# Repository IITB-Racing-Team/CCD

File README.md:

# Overview
### Contains all the files related to Electrical System of IITB-Racing.

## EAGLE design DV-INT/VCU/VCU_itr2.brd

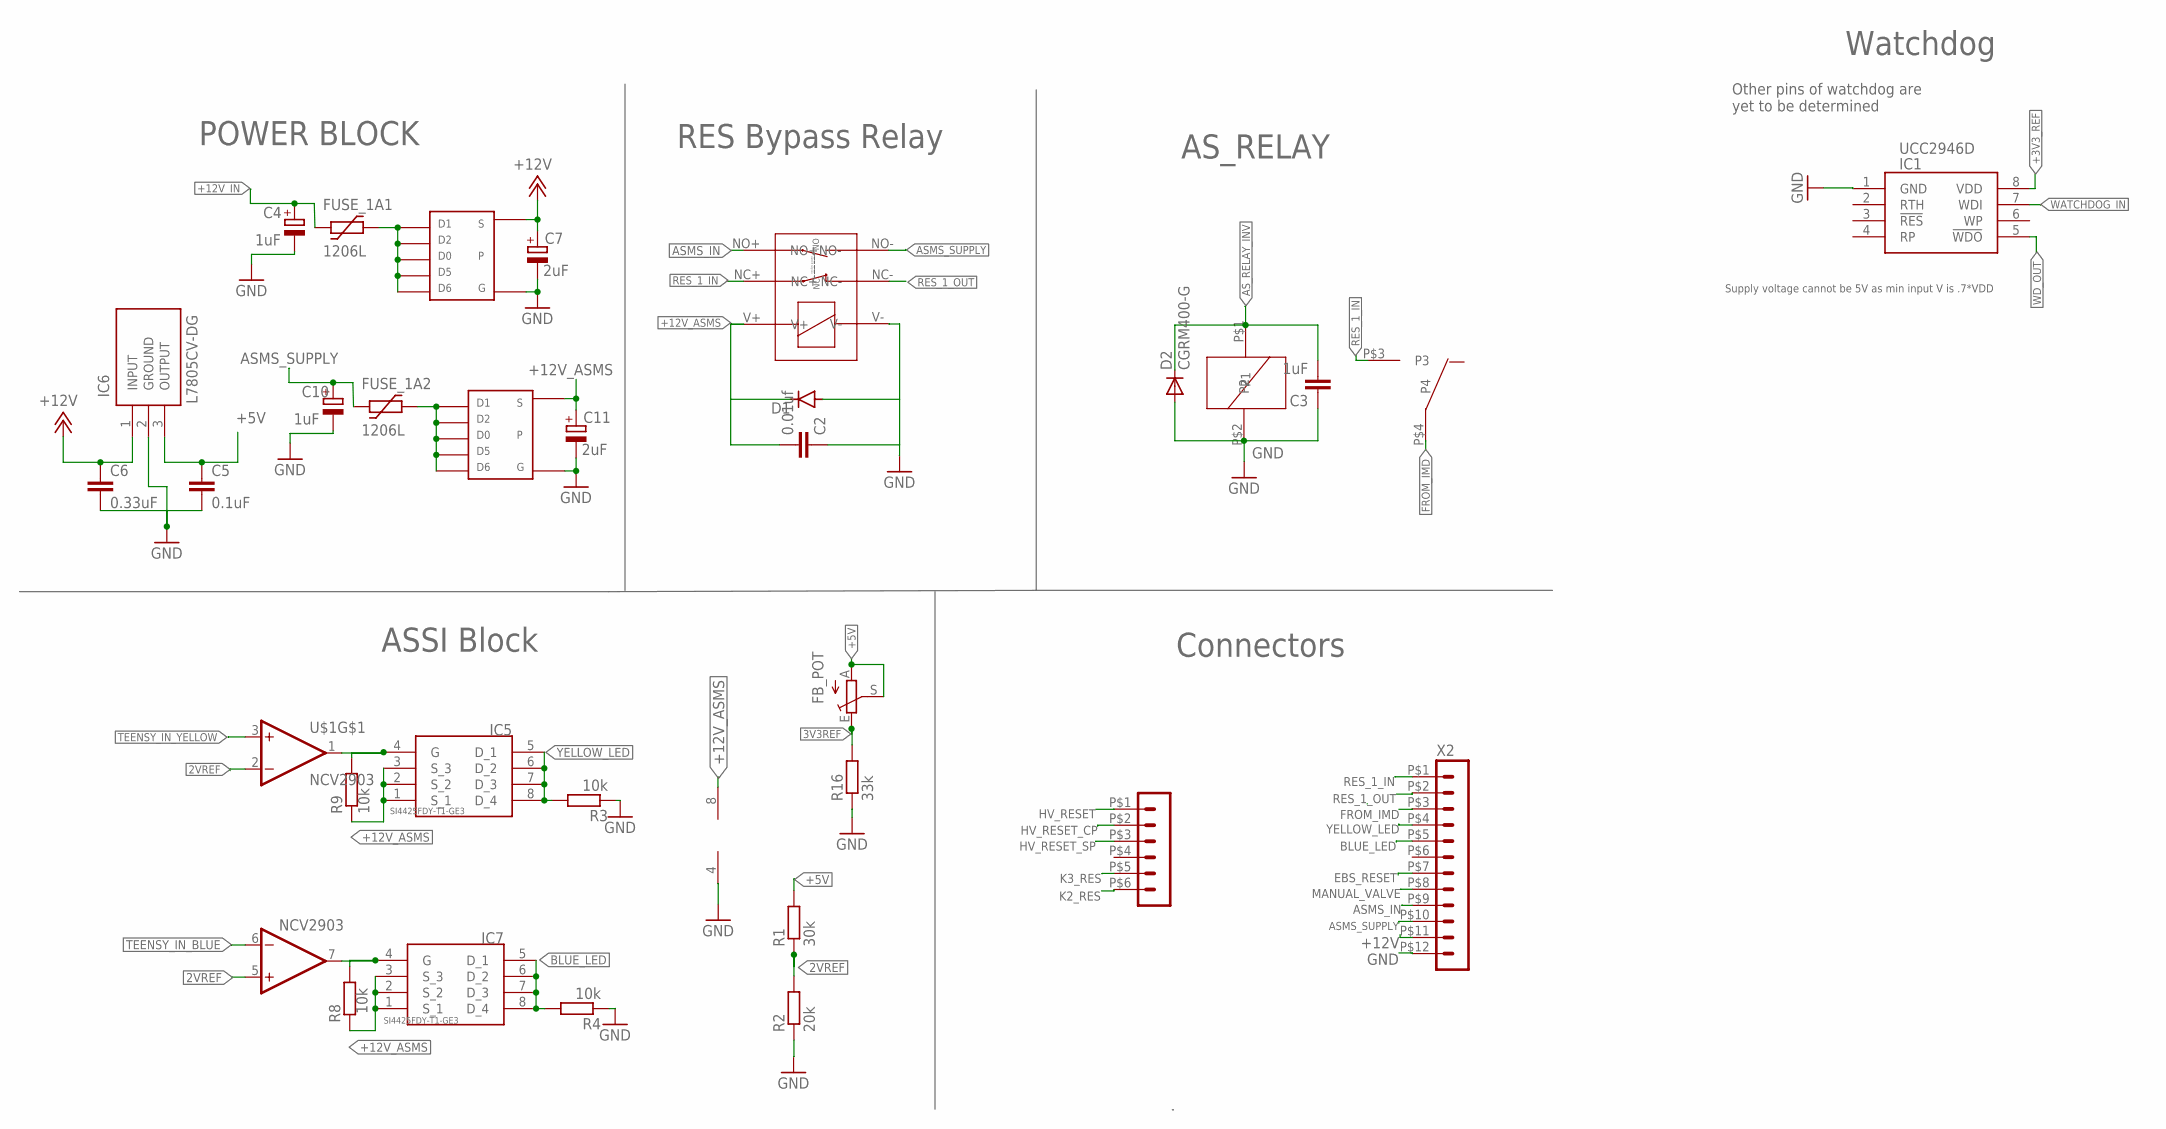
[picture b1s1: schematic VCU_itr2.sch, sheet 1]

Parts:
BMS-CONN7: HEADER_POS6_43045-0612; 43045-0612
C2: 0.01uf; C1210
C3: 1uF; C0805
C4, C10: 1uF; SMC_A
C5: 0.1uF; C0805
C6: 0.33uF; C0805
C7, C11: 2uF; E2,5-6
D1: DIODE-DO214AC; DO214AC
D2: CGRM400-G; SOD-123_MINI-SMA
FB_POT: 17k; S63S
FUSE_1A1, FUSE_1A2: 1206L
IC1: UCC2946D; SOIC127P600X175-8N
IC5, IC7: SI4425FDY-T1-GE3; SOIC127P600X175-8N
IC6: L7805CV-DG; TO255P460X1020X2008-3P
R1: 30k; M0805
R2: 20k; M0805
R3, R4, R8, R9: 10k; M0805
R16: 33k; M0805
SI1, SI4: TSOP-6_PMOS
U$1: NCV2903; SOIC-8
U$2: G6DN_RELAY
U$9: SFM_RELAY
X2: HEADER_POS12_44914-1201; 44914-1201

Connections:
2VREF: R1.1, R2.2, U$1.2 (-IN), U$1.5 (+IN); also elsewhere on the board
3V3REF: FB_POT.E, R16.2; also elsewhere on the board
+3V3_REF: IC1.8 (VDD)
+5V: C5.1, FB_POT.A, FB_POT.S, IC6.3 (OUTPUT), R1.2; also elsewhere on the board
+12V: C6.1, C7.+, IC6.1 (INPUT), SI1.S, X2.P$11 (11); also elsewhere on the board
+12V_ASMS: C2.2, C11.+, D1.C, IC5.1 (S_1), IC5.2 (S_2), IC5.3 (S_3), IC7.1 (S_1), IC7.2 (S_2), IC7.3 (S_3), R8.1, R9.1, SI4.S, U$1.8 (V+), U$9.V+; also elsewhere on the board
+12V_IN: C4.+, FUSE_1A1.P$1 (1)
ASMS_IN: U$9.NO+, X2.P$9 (9)
ASMS_SUPPLY: C10.+, FUSE_1A2.P$1 (1), U$9.NO-, X2.P$10 (10)
AS_RELAY_INV: C3.2, D2.C, U$2.P$1 (P1); also elsewhere on the board
BLUE_LED: IC7.5 (D_1), IC7.6 (D_2), IC7.7 (D_3), IC7.8 (D_4), R4.2, X2.P$5 (5)
EBS_RESET: X2.P$7 (7)
FROM_IMD: U$2.P$4 (P4), X2.P$3 (3)
GND: C2.1, C3.1, C4.-, C5.2, C6.2, C7.-, C10.-, C11.-, D1.A, D2.A, IC1.1 (GND), IC6.2 (GROUND), R2.1, R3.1, R4.1, R16.1, SI1.G, SI4.G, U$1.4 (V-), U$2.P$2 (P2), U$9.V-, X2.P$12 (12); also elsewhere on the board
HV_RESET: BMS-CONN7.P$1 (1); also elsewhere on the board
HV_RESET_CP: BMS-CONN7.P$2 (2); also elsewhere on the board
HV_RESET_SP: BMS-CONN7.P$3 (3); also elsewhere on the board
K2_RES: BMS-CONN7.P$6 (6)
K3_RES: BMS-CONN7.P$5 (5)
MANUAL_VALVE: X2.P$8 (8); also elsewhere on the board
unnamed: IC7.4 (G), R8.2, U$1.7 (OUT)
unnamed: IC5.4 (G), R9.2, U$1.1 (OUT)
unnamed: FUSE_1A2.P$2 (2), SI4.1, SI4.2, SI4.5, SI4.6, SI4.D (D0)
unnamed: FUSE_1A1.P$2 (2), SI1.1, SI1.2, SI1.5, SI1.6, SI1.D (D0)
RES_1_IN: U$2.P$3 (P3), U$9.NC+, X2.P$1 (1)
RES_1_OUT: U$9.NC-, X2.P$2 (2)
TEENSY_IN_BLUE: U$1.6 (-IN)
TEENSY_IN_YELLOW: U$1.3 (+IN)
WATCHDOG_IN: IC1.7 (WDI)
WD_OUT: IC1.5 (!WDO); also elsewhere on the board
YELLOW_LED: IC5.5 (D_1), IC5.6 (D_2), IC5.7 (D_3), IC5.8 (D_4), R3.2, X2.P$4 (4)

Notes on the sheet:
POWER BLOCK
ASSI Block
RES Bypass Relay
Watchdog
Other pins of watchdog are yet to be determined
Supply voltage cannot be 5V as min input V is .7*VDD
Connectors
AS_RELAY

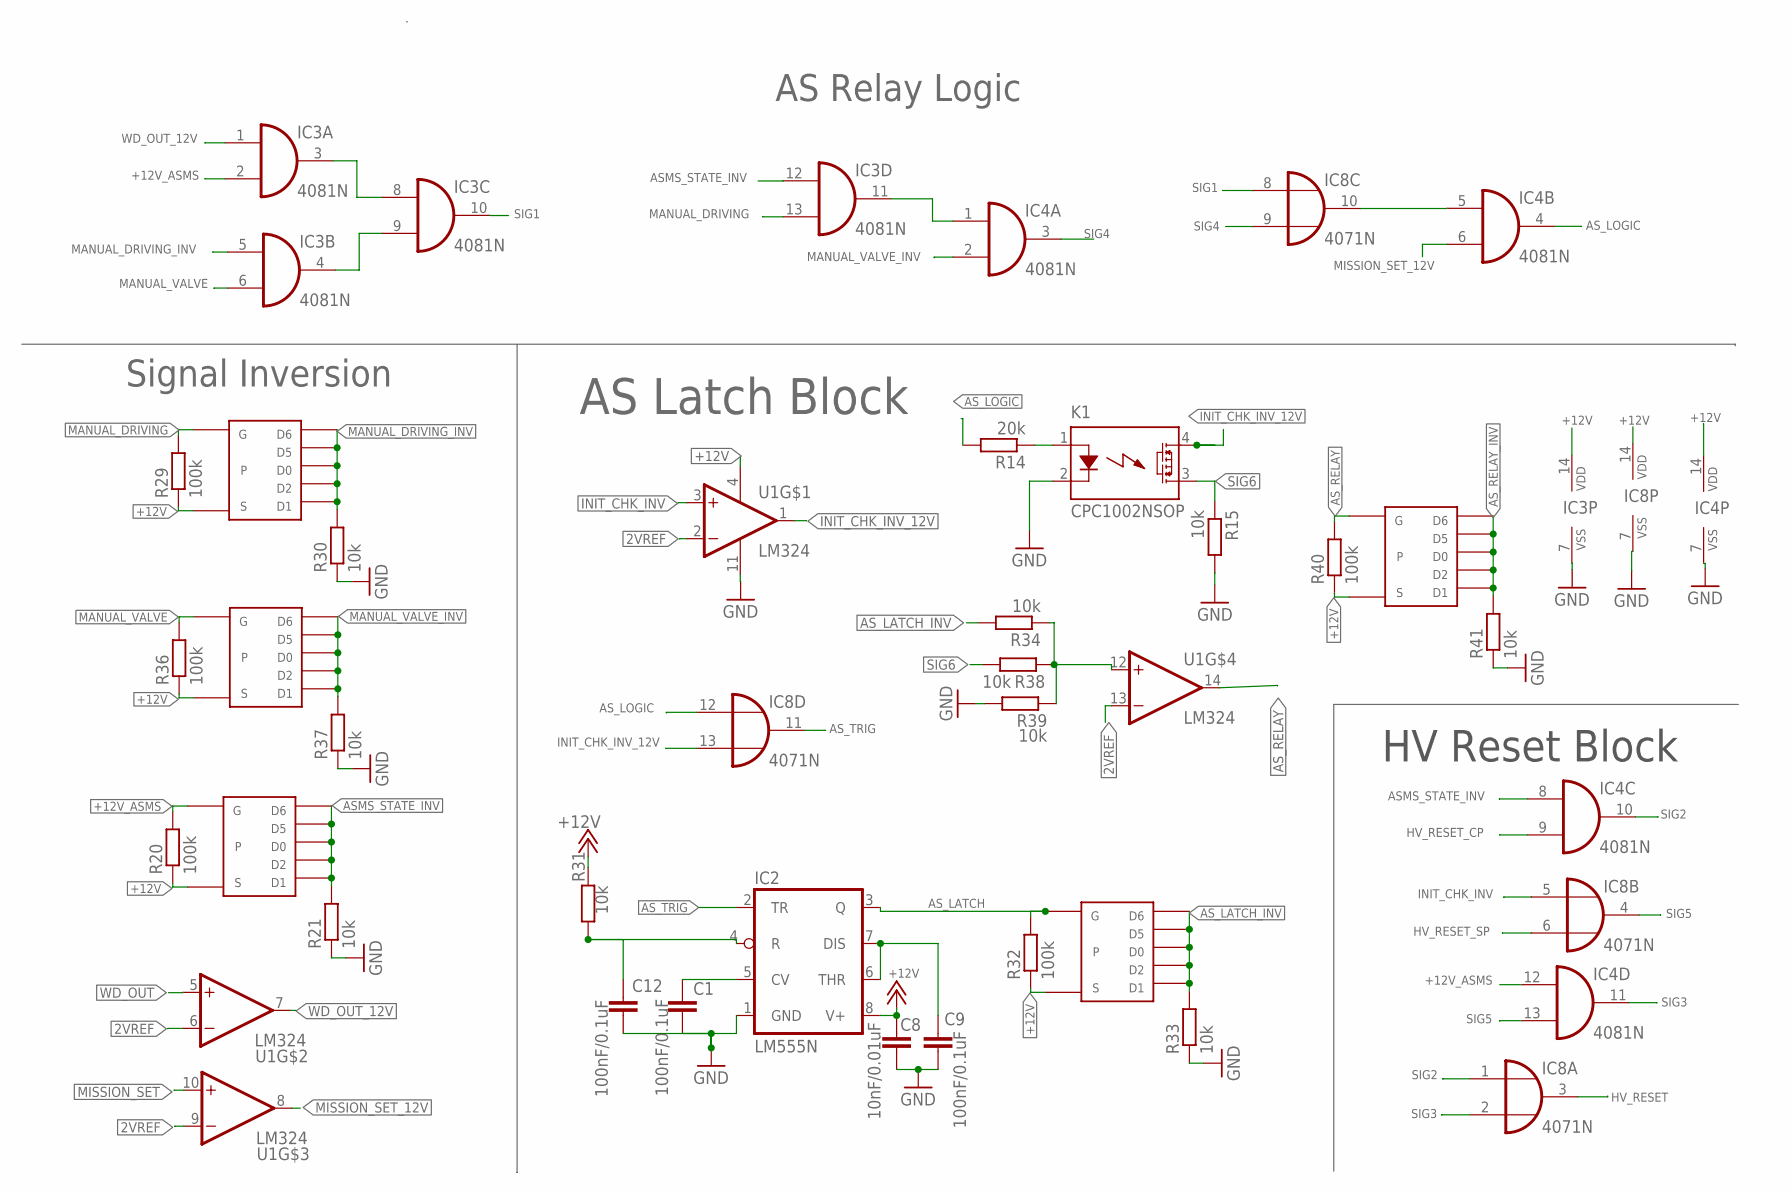
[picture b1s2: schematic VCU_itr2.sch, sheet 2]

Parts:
C1, C9, C12: 100nF/0.1uF; C0805
C8: 10nF/0.01uF; C0805
IC2: LM555N; DIL08
IC3, IC4: 4081N; DIL14
IC8: 4071N; DIL14
K1: CPC1002NSOP; SOP04
R14: 20k; R0805
R15, R31: 10k; R0805
R20, R29, R32, R36, R40: 100k; M0805
R21, R30, R33, R34, R37, R38, R39, R41: 10k; M0805
SI2, SI3, SI5, SI6, SI7: TSOP-6_PMOS
U1: LM324; SOIC127P600X175-14N

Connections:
2VREF: U1.2 (INVERTING_INPUT1), U1.6 (INVERTING_INPUT2), U1.9 (INVERTING_INPUT3), U1.13 (INVERTING_INPUT4); also elsewhere on the board
+12V: C8.1, IC2.8 (V+), IC3.14 (VDD), IC4.14 (VDD), IC8.14 (VDD), R20.1, R29.1, R31.2, R32.1, R36.1, R40.1, SI2.S, SI3.S, SI5.S, SI6.S, SI7.S, U1.4 (VCC+); also elsewhere on the board
+12V_ASMS: IC3.2 (I1), IC4.12 (I0), R20.2, SI5.G; also elsewhere on the board
ASMS_STATE_INV: IC3.12 (I0), IC4.8 (I0), R21.2, SI5.1, SI5.2, SI5.5, SI5.6, SI5.D (D0)
AS_LATCH: IC2.3 (Q), R32.2, SI2.G
AS_LATCH_INV: R33.2, R34.2, SI2.1, SI2.2, SI2.5, SI2.6, SI2.D (D0)
AS_LOGIC: IC4.4 (O), IC8.12 (I0), R14.2
AS_RELAY: R40.2, SI3.G, U1.14 (OUTPUT4)
AS_RELAY_INV: R41.2, SI3.1, SI3.2, SI3.5, SI3.6, SI3.D (D0); also elsewhere on the board
AS_TRIG: IC2.2 (TR), IC8.11 (O)
GND: C1.2, C8.2, C9.2, C12.2, IC2.1 (GND), IC3.7 (VSS), IC4.7 (VSS), IC8.7 (VSS), K1.2 (K), R15.2, R21.1, R30.1, R33.1, R37.1, R39.2, R41.1, U1.11 (VCC-); also elsewhere on the board
HV_RESET: IC8.3 (O); also elsewhere on the board
HV_RESET_CP: IC4.9 (I1); also elsewhere on the board
HV_RESET_SP: IC8.6 (I1); also elsewhere on the board
INIT_CHK_INV: IC8.5 (I0), U1.3 (NON-INVERTING_INPUT1)
INIT_CHK_INV_12V: IC8.13 (I1), K1.4 (DS1), U1.1 (OUTPUT1)
MANUAL_DRIVING: IC3.13 (I1), R29.2, SI6.G; also elsewhere on the board
MANUAL_DRIVING_INV: IC3.5 (I0), R30.2, SI6.1, SI6.2, SI6.5, SI6.6, SI6.D (D0)
MANUAL_VALVE: IC3.6 (I1), R36.2, SI7.G; also elsewhere on the board
MANUAL_VALVE_INV: IC4.2 (I1), R37.2, SI7.1, SI7.2, SI7.5, SI7.6, SI7.D (D0)
MISSION_SET: U1.10 (NON-INVERTING_INPUT3)
MISSION_SET_12V: IC4.6 (I1), U1.8 (OUTPUT3)
unnamed: IC4.5 (I0), IC8.10 (O)
unnamed: IC3.3 (O), IC3.8 (I0)
unnamed: IC3.4 (O), IC3.9 (I1)
unnamed: IC3.11 (O), IC4.1 (I0)
unnamed: K1.1 (A), R14.1
unnamed: R34.1, R38.1, R39.1, U1.12 (NON-INVERTING_INPUT4)
unnamed: C12.1, IC2.4 (R), R31.1
unnamed: C1.1, IC2.5 (CV)
unnamed: C9.1, IC2.6 (THR), IC2.7 (DIS)
SIG1: IC3.10 (O), IC8.8 (I0)
SIG2: IC4.10 (O), IC8.1 (I0)
SIG3: IC4.11 (O), IC8.2 (I1)
SIG4: IC4.3 (O), IC8.9 (I1)
SIG5: IC4.13 (I1), IC8.4 (O)
SIG6: K1.3 (DS2), R15.1, R38.2
WD_OUT: U1.5 (NON-INVERTING_INPUT2); also elsewhere on the board
WD_OUT_12V: IC3.1 (I0), U1.7 (OUTPUT2)

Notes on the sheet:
AS Relay Logic
Signal Inversion
AS Latch Block
HV Reset Block

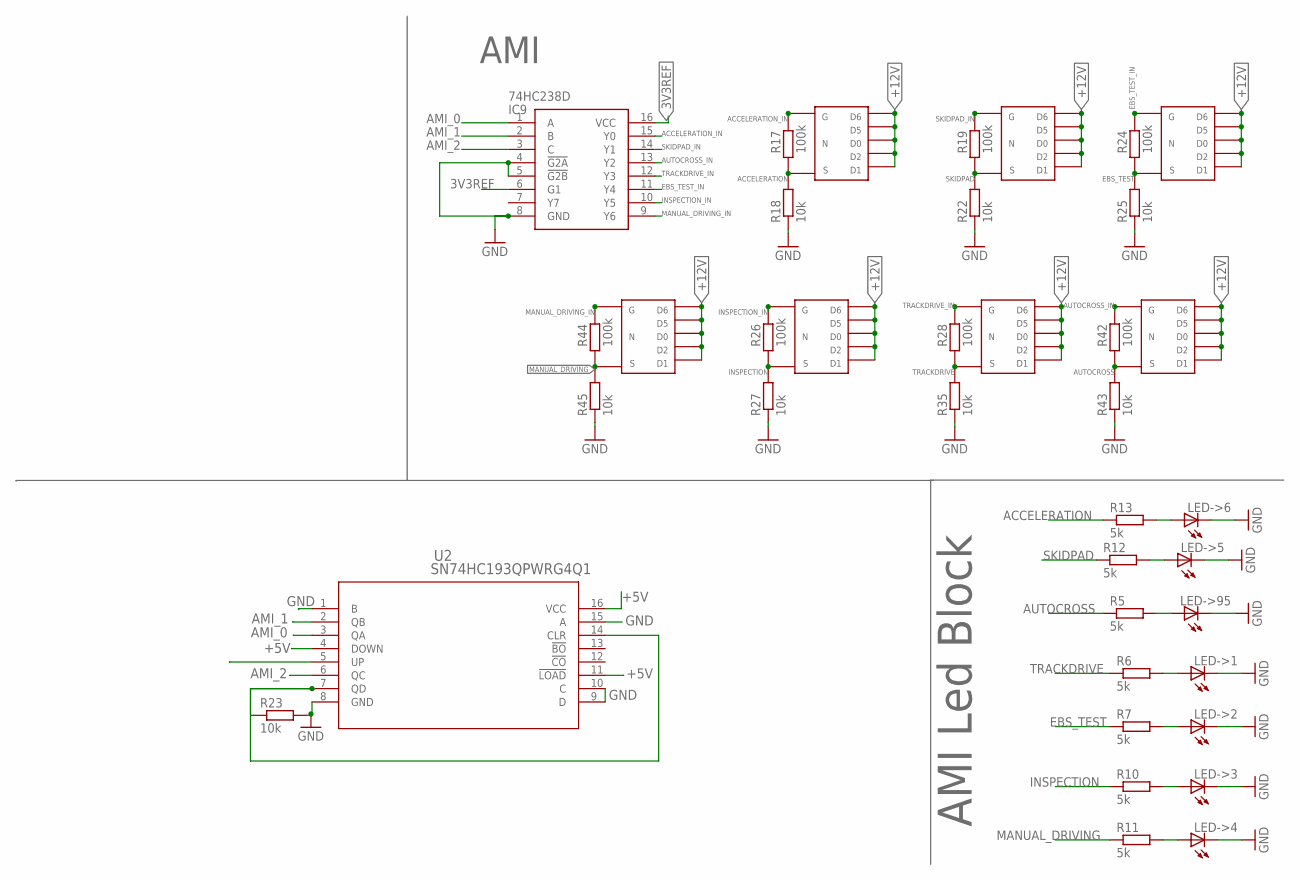
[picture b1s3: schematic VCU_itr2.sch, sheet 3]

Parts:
IC9: 74HC238D; SOIC127P600X175-16N
LED->1, LED->2, LED->3, LED->4, LED->5, LED->6, LED->95: LED-FKIT-1206; FKIT-LED-1206
R5, R6, R7, R10, R11, R12, R13: 5k; R0805
R17, R19, R24, R26, R28, R42, R44: 100k; R0805
R18, R22, R23, R25, R27, R35, R43, R45: 10k; M0805
U2: SN74HC193QPWRG4Q1; PW16
U$13, U$14, U$15, U$16, U$17, U$18, U$19: TSOP-6_NMOS

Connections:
3V3REF: IC9.6 (G1), IC9.16 (VCC); also elsewhere on the board
+5V: U2.4 (DOWN), U2.11 (!LOAD), U2.16 (VCC); also elsewhere on the board
+12V: U$13.1, U$13.2, U$13.5, U$13.6, U$13.D (D0), U$14.1, U$14.2, U$14.5, U$14.6, U$14.D (D0), U$15.1, U$15.2, U$15.5, U$15.6, U$15.D (D0), U$16.1, U$16.2, U$16.5, U$16.6, U$16.D (D0), U$17.1, U$17.2, U$17.5, U$17.6, U$17.D (D0), U$18.1, U$18.2, U$18.5, U$18.6, U$18.D (D0), U$19.1, U$19.2, U$19.5, U$19.6, U$19.D (D0); also elsewhere on the board
ACCELERATION: R13.1, R17.1, R18.2, U$13.S
ACCELERATION_IN: IC9.15 (Y0), R17.2, U$13.G
AMI_0: IC9.1 (A), U2.3 (QA)
AMI_1: IC9.2 (B), U2.2 (QB)
AMI_2: IC9.3 (C), U2.6 (QC)
AUTOCROSS: R5.1, R42.1, R43.2, U$18.S
AUTOCROSS_IN: IC9.13 (Y2), R42.2, U$18.G
EBS_TEST: R7.1, R24.1, R25.2, U$15.S
EBS_TEST_IN: IC9.11 (Y4), R24.2, U$15.G
GND: IC9.4 (!G2A), IC9.5 (!G2B), IC9.8 (GND), LED->1.C, LED->2.C, LED->3.C, LED->4.C, LED->5.C, LED->6.C, LED->95.C, R18.1, R22.1, R23.2, R25.1, R27.1, R35.1, R43.1, R45.1, U2.1 (B), U2.8 (GND), U2.9 (D), U2.10 (C), U2.15 (A); also elsewhere on the board
INSPECTION: R10.1, R26.1, R27.2, U$16.S
INSPECTION_IN: IC9.10 (Y5), R26.2, U$16.G
MANUAL_DRIVING: R11.1, R44.1, R45.2, U$19.S; also elsewhere on the board
MANUAL_DRIVING_IN: IC9.9 (Y6), R44.2, U$19.G
unnamed: LED->2.A, R7.2
unnamed: LED->4.A, R11.2
unnamed: LED->1.A, R6.2
unnamed: LED->3.A, R10.2
unnamed: LED->5.A, R12.2
unnamed: LED->6.A, R13.2
unnamed: R23.1, U2.7 (QD), U2.14 (CLR)
unnamed: LED->95.A, R5.2
SKIDPAD: R12.1, R19.1, R22.2, U$14.S
SKIDPAD_IN: IC9.14 (Y1), R19.2, U$14.G
TRACKDRIVE: R6.1, R28.1, R35.2, U$17.S
TRACKDRIVE_IN: IC9.12 (Y3), R28.2, U$17.G

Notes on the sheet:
AMI Led Block
AMI

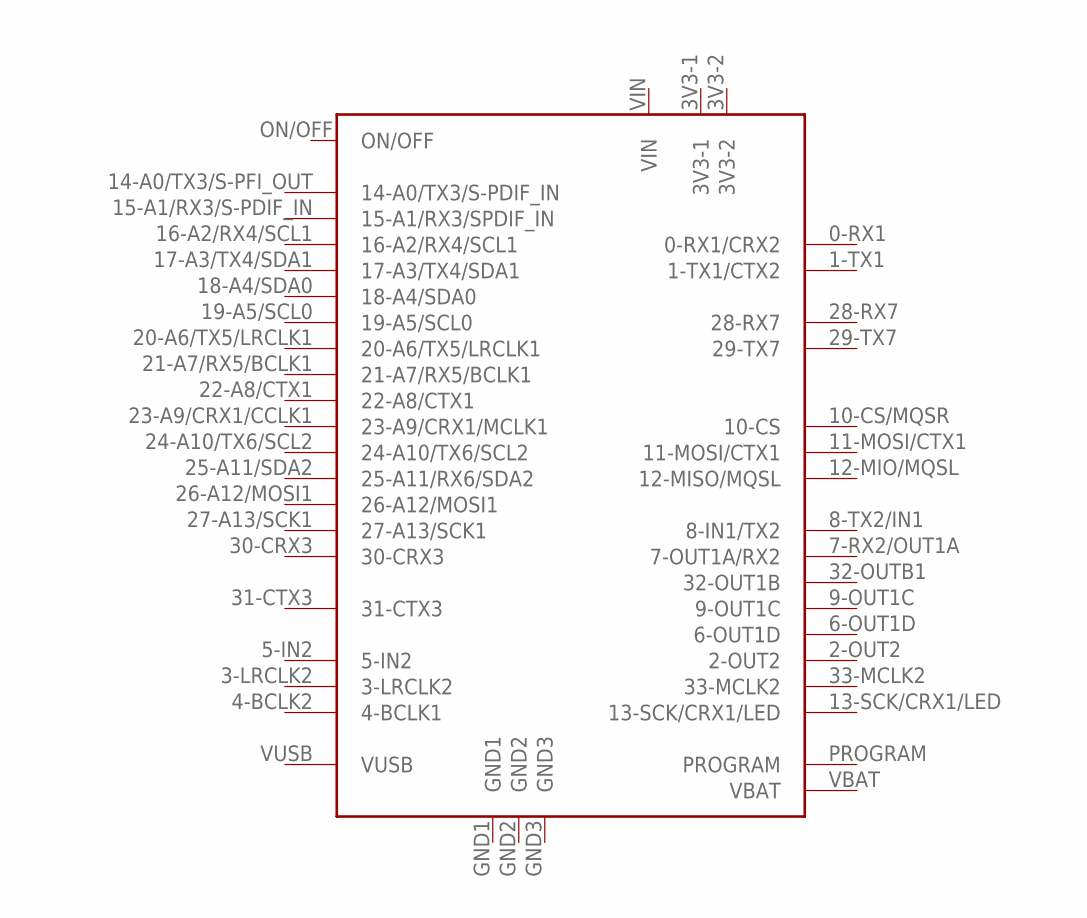
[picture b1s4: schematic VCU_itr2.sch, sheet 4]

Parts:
U$3: TEENSY40

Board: 2 copper layers, 101 parts (0 on the bottom side), 76 nets, no tracks yet.

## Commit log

2024-10-08 Added new files to Data_analysis
2024-10-08 modified
2024-10-08 CAN CODE FOR MASTER
2024-10-10 VCU Schematic Updated
2024-10-10 Testing branch
2024-10-10 updating gitginore

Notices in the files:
parts and their libraries:
COPYRIGHT: Copyright (C) 2024 Ultra Librarian. All rights reserved.
